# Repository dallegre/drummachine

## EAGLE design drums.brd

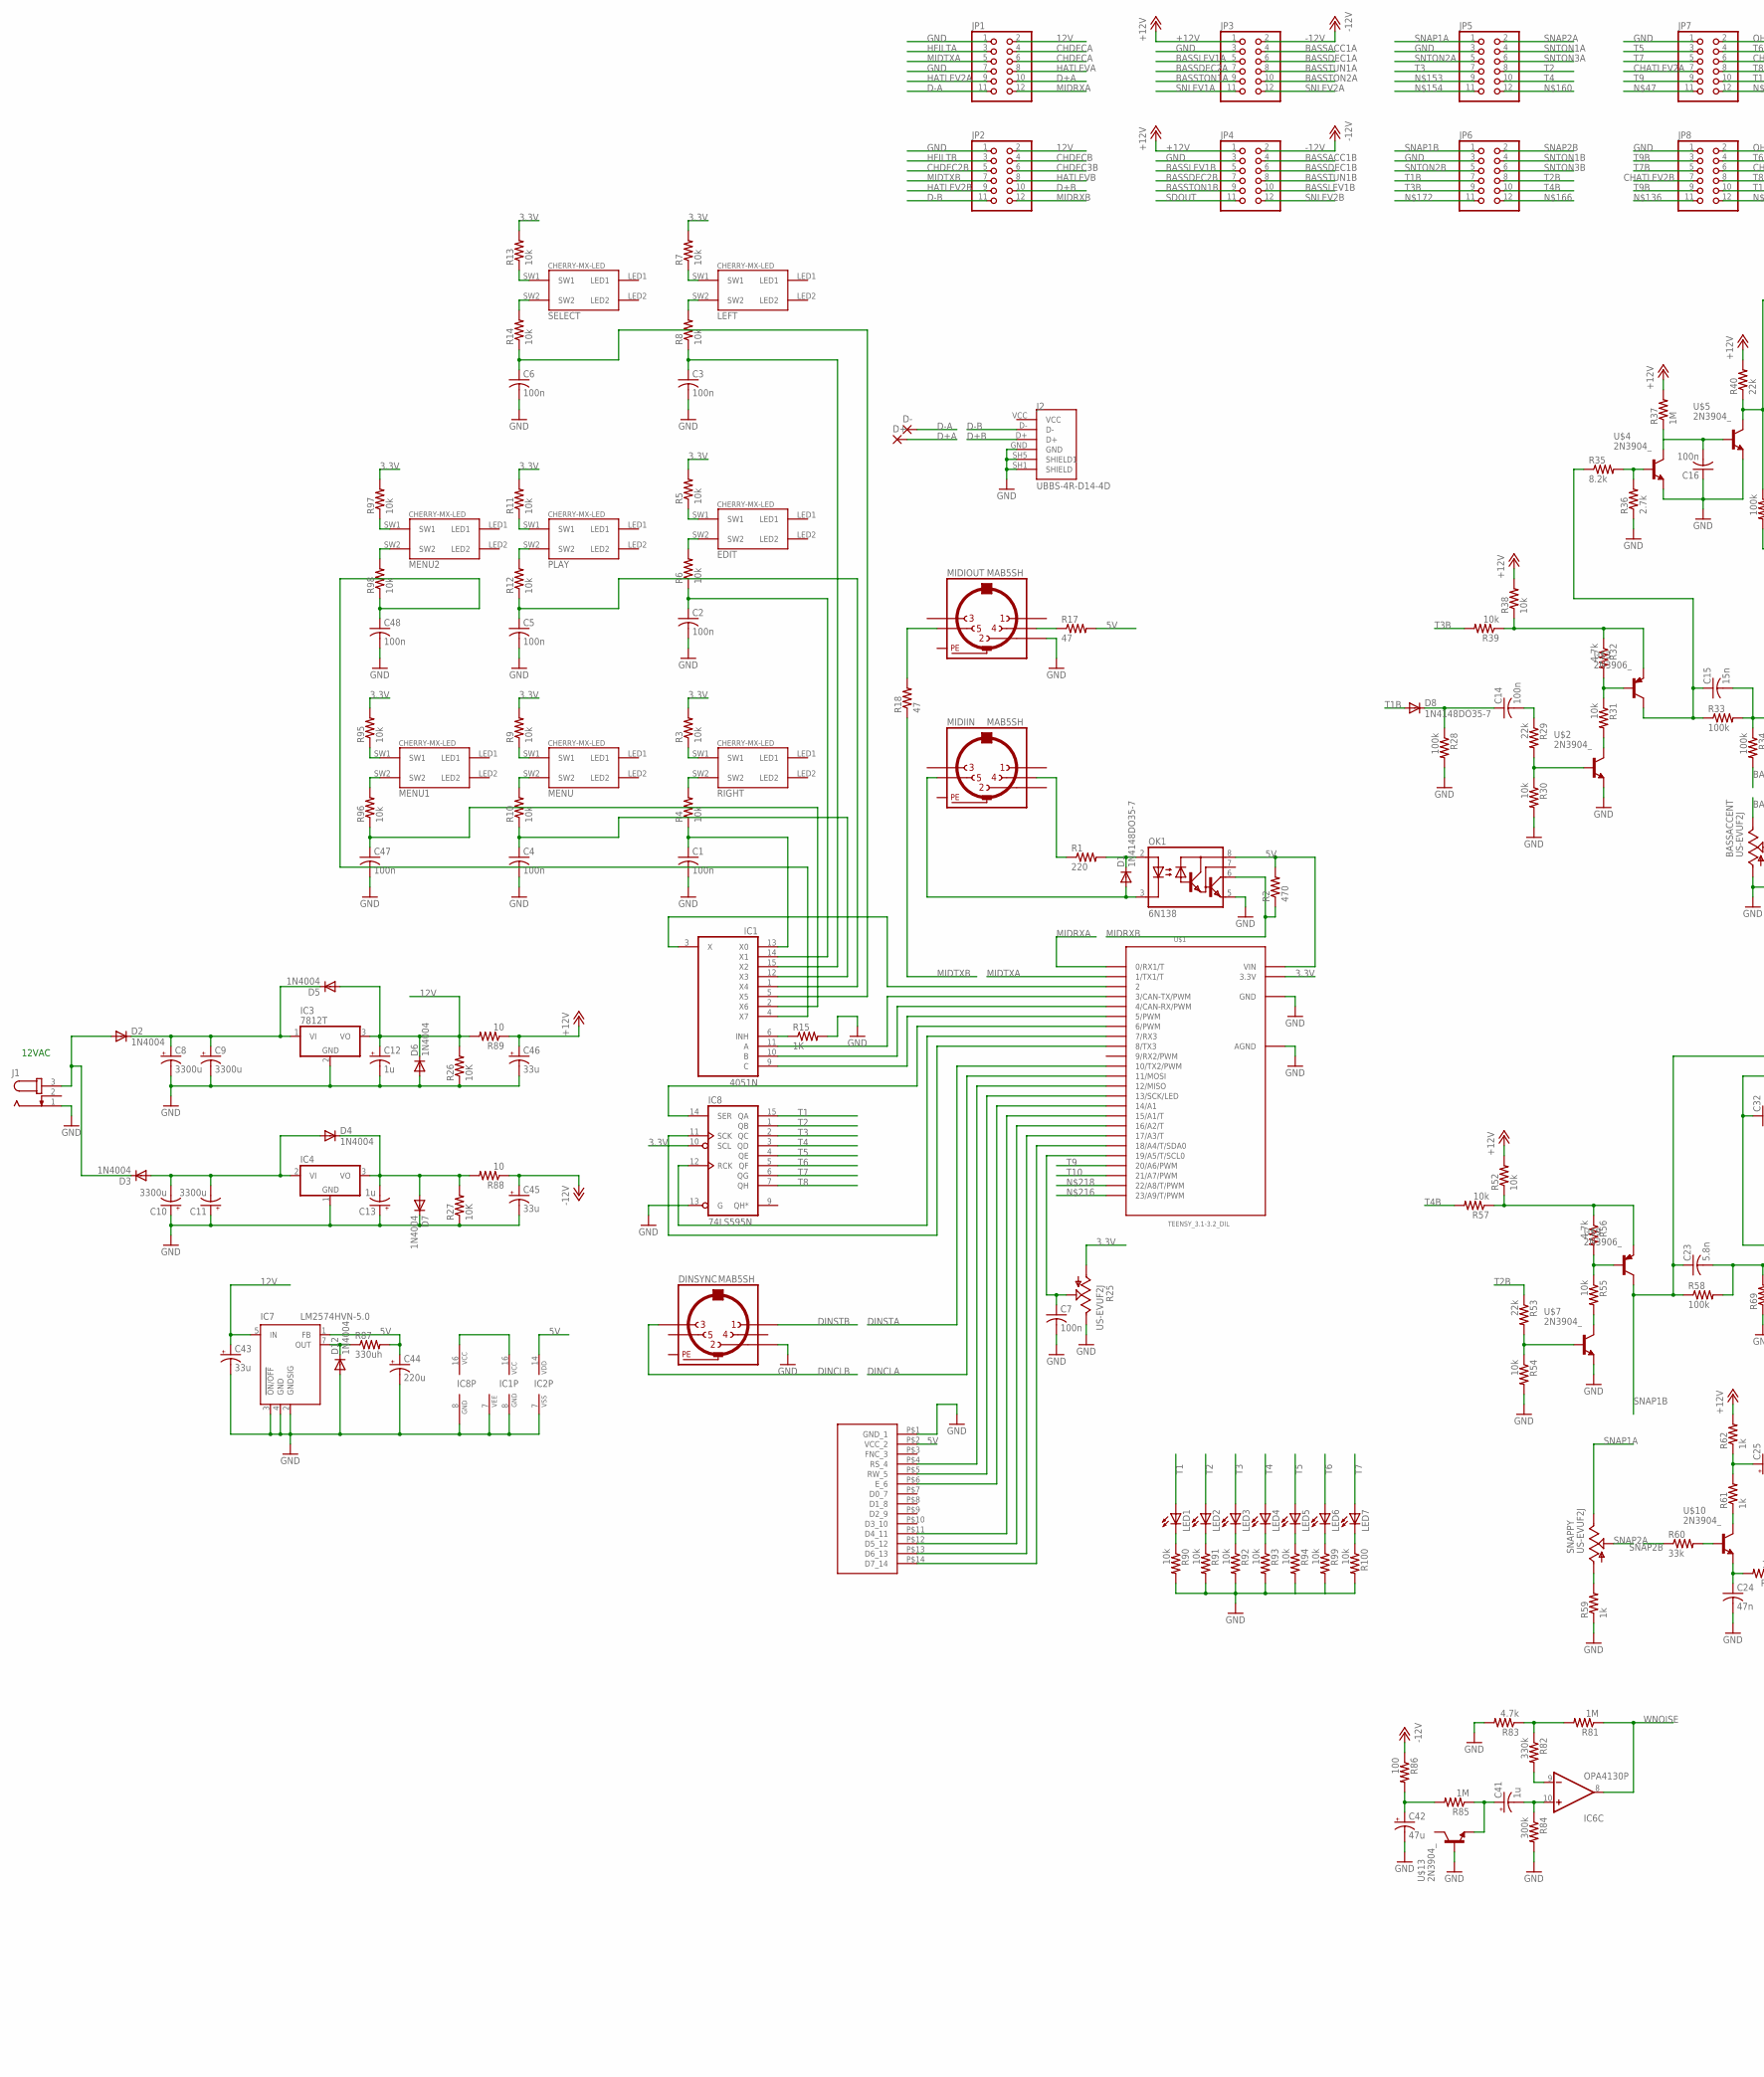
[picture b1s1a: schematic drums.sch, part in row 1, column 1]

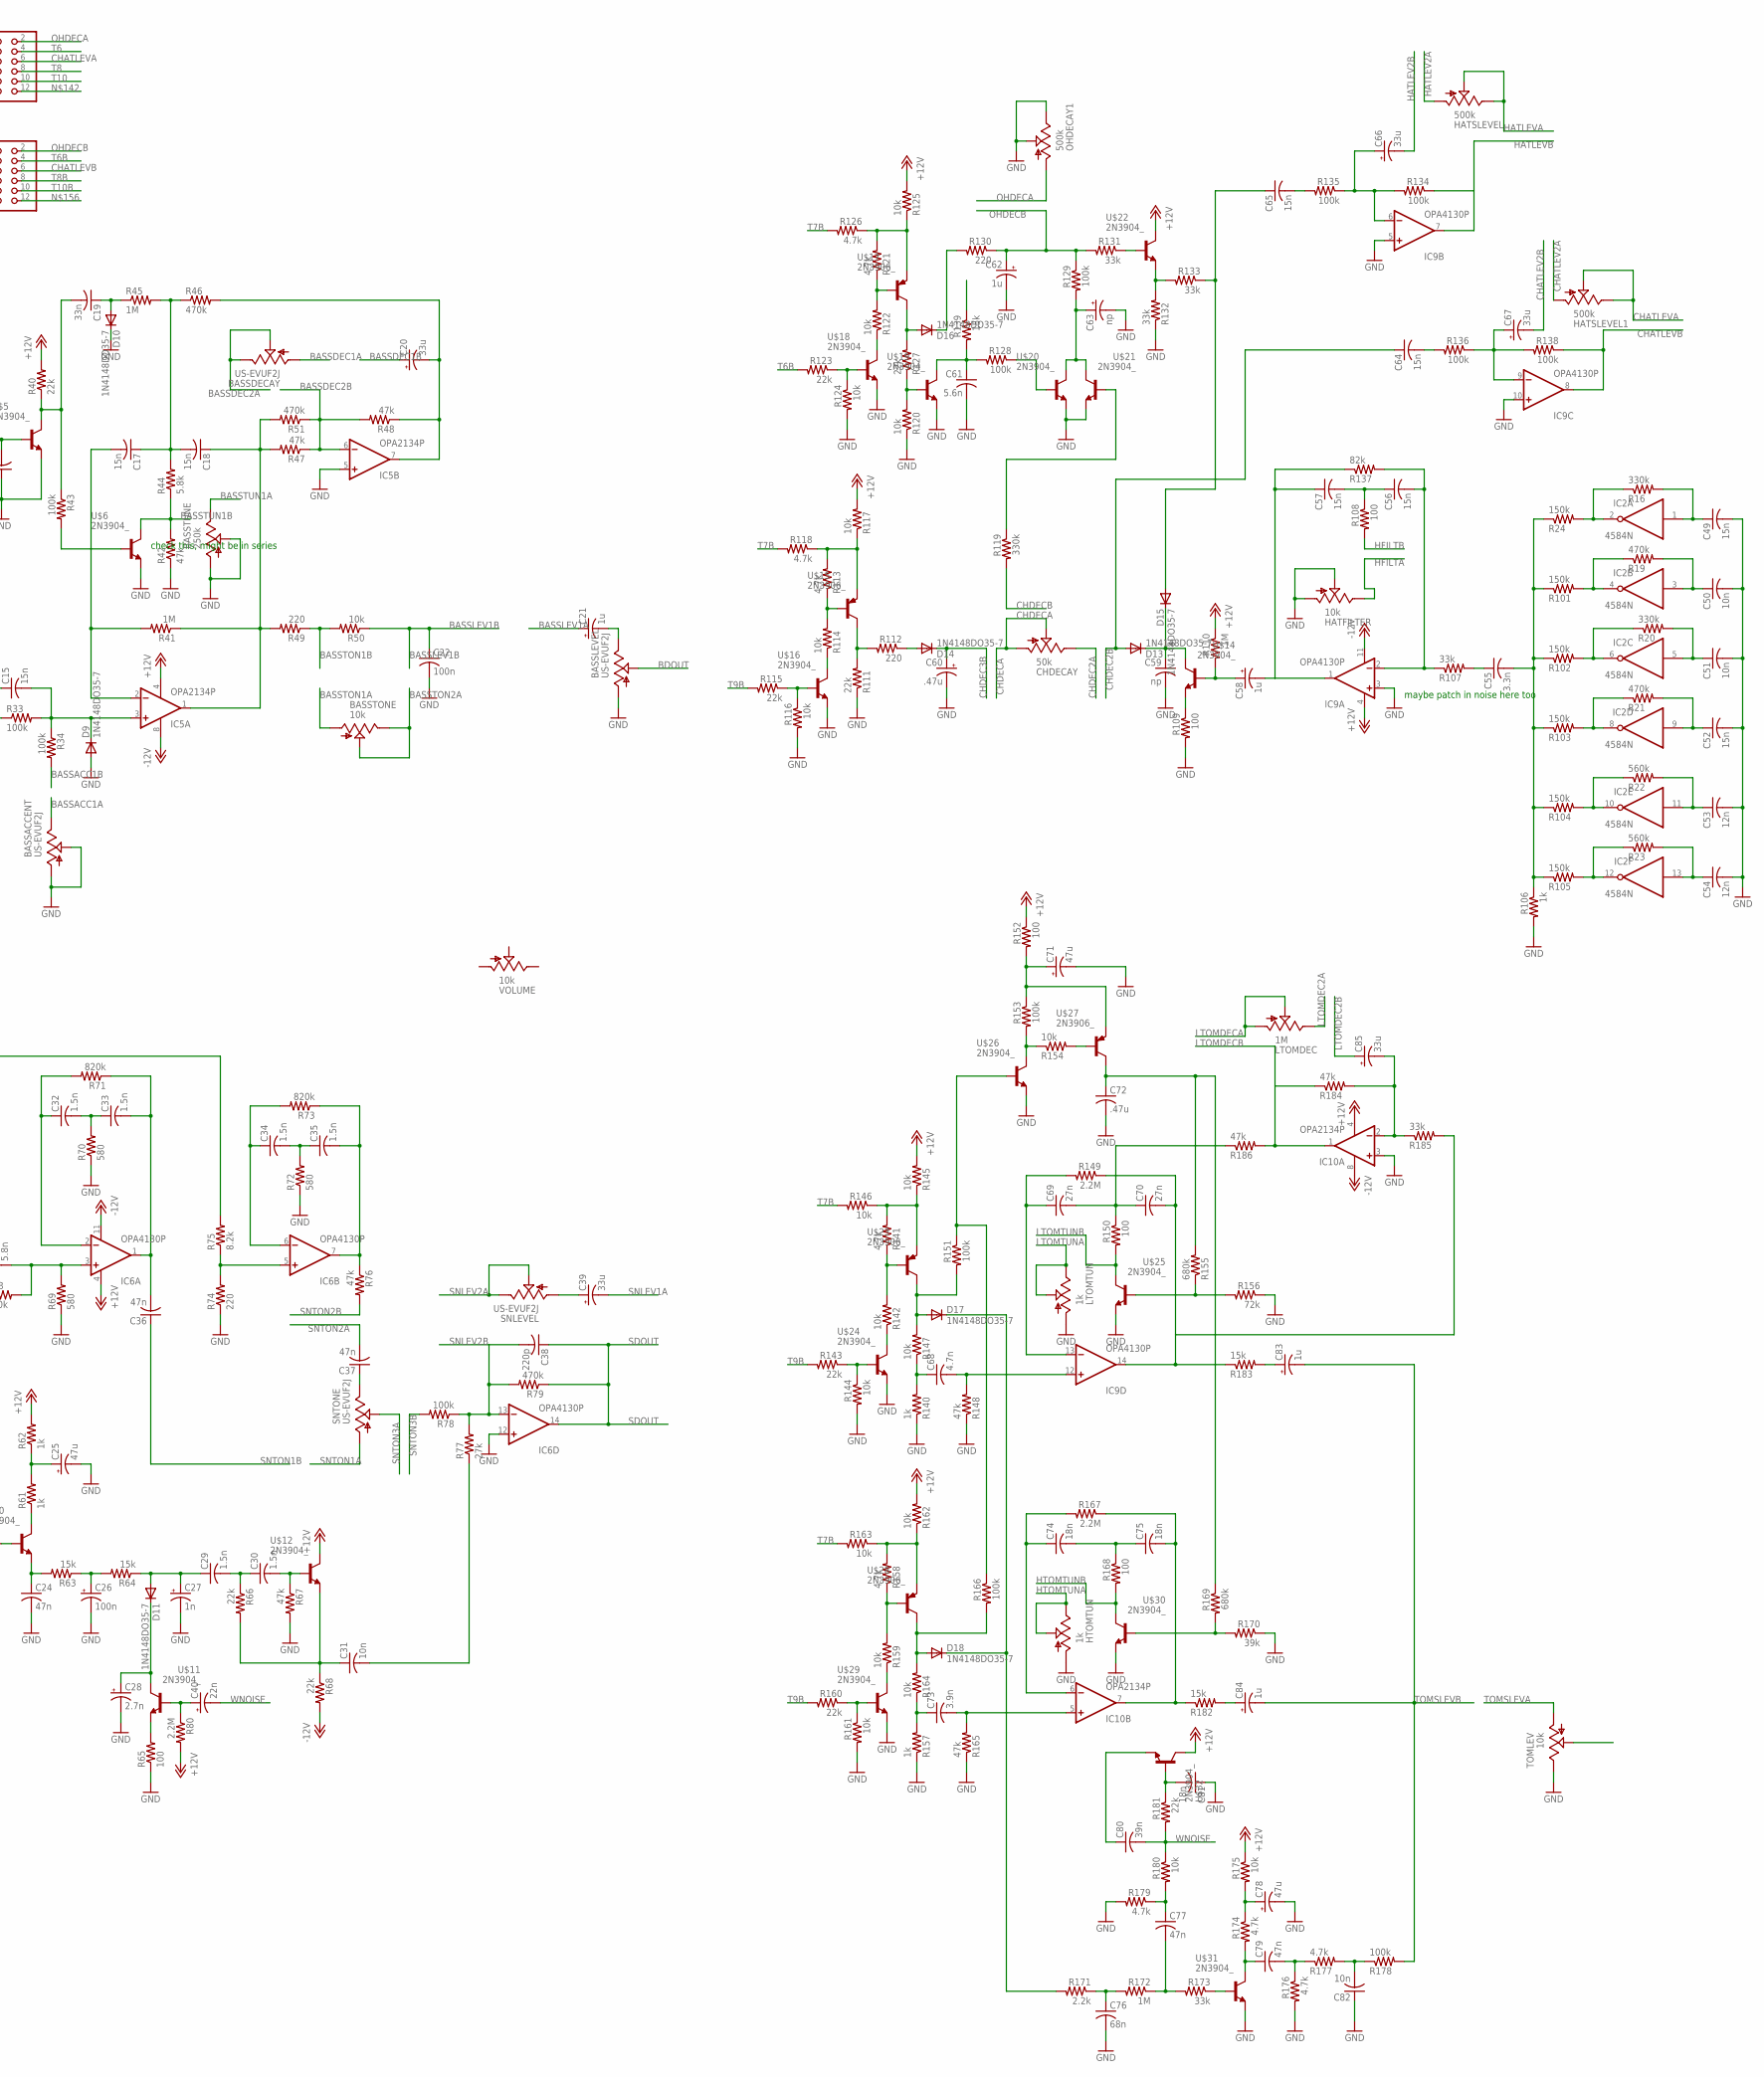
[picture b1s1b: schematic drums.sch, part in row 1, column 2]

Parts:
BASSACCENT: US-EVUF2J; EVUFXJ
BASSDECAY: US-EVUF2J; EVUFXJ
BASSLEVEL: US-EVUF2J; EVUFXJ
BASSTONE: 10k; EVUFXJ
BASSTUNE: 250k; EVUFXJ
C1, C2, C3, C4, C5, C6, C7, C14, C16, C22, C47, C48: 100n; C050-025X075
C8, C9, C10, C11: 3300u; E5-10,5
C12, C13, C21, C41, C58, C62, C83, C84: 1u; E2-5
C15, C17, C18, C49, C52, C56, C57, C64, C65: 15n; C050-025X075
C19: 33n; C050-025X075
C20, C39, C43, C45, C46, C66, C67, C85: 33u; E2-5
C23: 5.8n; C050-025X075
C24, C36, C37, C77, C79: 47n; C050-025X075
C25, C42, C71, C78: 47u; E2-5
C26: 100n; E2-5
C27: 1n; E2-5
C28: 2.7n; E2-5
C29, C30, C32, C33, C34, C35: 1.5n; C050-025X075
C31, C50, C51, C82: 10n; C050-025X075
C38: 220p; C050-025X075
C40: 22n; E2-5
C44: 220u; E2-5
C53, C54: 12n; C050-025X075
C55: 3.3n; C050-025X075
C59: np; C050-025X075
C60: .47u; E2-5
C61: 5.6n; C050-025X075
C63: np; E2-5
C68: 4.7n; C050-025X075
C69, C70: 27n; C050-025X075
C72: .47u; C050-025X075
C73: 3.9n; C050-025X075
C74, C75, C81: 18n; C050-025X075
C76: 68n; C050-025X075
C80: 39n; C050-025X075
CHDECAY: 50k; EVUFXJ
D1, D8, D9, D10, D11, D13, D14, D15, D16, D17, D18: 1N4148DO35-7; DO35-7
D2, D3, D4, D5, D6, D7, D12: 1N4004; DO41-10
D+: 2,0/0,9-R
D-: 2,0/0,9-R
DINSYNC: MAB5SH
EDIT: CHERRY-MX-LED
HATFILTER: 10k; EVUFXJ
HATSLEVEL, HATSLEVEL1: 500k; EVUFXJ
HTOMTUN: 1k; EVUFXJ
IC1: 4051N; DIL16
IC2: 4584N; DIL14
IC3: 7812T; TO220H
IC4: 7906T; TO220H
IC5, IC10: OPA2134P; DIL08
IC6, IC9: OPA4130P; DIL14
IC7: LM2574HVN-5.0; DIL08
IC8: 74LS595N; DIL16
J1: JACK-PLUG0; SPC4077
J2: UBBS-4R-D14-4D; JST_UBBS-4R-D14-4D
JP1, JP2, JP3, JP4, JP5, JP6, JP7, JP8: PINHD-2X6; 2X06
LED1, LED2, LED3, LED4, LED5, LED6, LED7: LED5MM
LEFT: CHERRY-MX-LED
LTOMDEC: 1M; EVUFXJ
LTOMTUN: 1k; EVUFXJ
MENU, MENU1, MENU2: CHERRY-MX-LED
MIDIIN: MAB5SH
MIDIOUT: MAB5SH
OHDECAY1: 500k; EVUFXJ
OK1: 6N138; DIL08
PLAY: CHERRY-MX-LED
R1, R49, R74, R112, R130: 220; 0207/2V
R2: 470; 0207/2V
R3, R4, R5, R6, R7, R8, R9, R10, R11, R12, R13, R14, R30, R31, R38, R39, R50, R52, R54, R55, R57, R90, R91, R92, R93, R94, R95, R96, R97, R98, R99, R100, R114, R116, R117, R120, R122, R124, R125, R142, R144, R145, R146, R147, R154, R159, R161, R162, R163, R164, R175, R180: 10k; 0207/2V
R15: 1K; 0207/2V
R16, R20, R82, R119: 330k; 0207/2V
R17, R18: 47; 0207/2V
R19, R21, R46, R51, R79: 470k; 0207/2V
R22, R23: 560k; 0207/2V
R24, R101, R102, R103, R104, R105: 150k; 0207/2V
R25: US-EVUF2J; EVUFXJ
R26, R27: 10K; 0207/7
R28, R33, R34, R43, R58, R78, R128, R129, R134, R135, R136, R138, R151, R153, R166, R178: 100k; 0207/2V
R29, R40, R53, R66, R68, R111, R115, R123, R127, R143, R160, R181: 22k; 0207/2V
R32, R56, R83, R113, R118, R121, R126, R141, R158, R174, R176, R177, R179: 4.7k; 0207/2V
R35, R75: 8.2k; 0207/2V
R36: 2.7k; 0207/2V
R37, R41, R45, R81, R85, R110, R172: 1M; 0207/2V
R42, R47, R48, R67, R76, R148, R165, R184, R186: 47k; 0207/2V
R44: 5.8k; 0207/2V
R59, R61, R62, R106, R140, R157: 1k; 0207/2V
R60, R107, R131, R132, R133, R173, R185: 33k; 0207/2V
R63, R64, R139, R182, R183: 15k; 0207/2V
R65, R86, R108, R109, R150, R152, R168: 100; 0207/2V
R69, R70, R72: 580; 0207/2V
R71, R73: 820k; 0207/2V
R77: 27k; 0207/2V
R80, R149, R167: 2.2M; 0207/2V
R84: 300k; 0207/2V
R87: 330uh; 0207/2V
R88, R89: 10; 0207/7
R137: 82k; 0207/2V
R155, R169: 680k; 0207/2V
R156: 72k; 0207/2V
R170: 39k; 0207/2V
R171: 2.2k; 0207/2V
RIGHT: CHERRY-MX-LED
SELECT: CHERRY-MX-LED
SNAPPY: US-EVUF2J; EVUFXJ
SNLEVEL: US-EVUF2J; EVUFXJ
SNTONE: US-EVUF2J; EVUFXJ
TOMLEV: 10k; EVUFXJ
U$1: TEENSY_3.1-3.2_DIL; TEENSY_3.0-3.2&LC_DIL
U$2, U$4, U$5, U$6, U$7, U$10, U$11, U$12, U$13, U$14, U$16, U$18, U$19, U$20, U$21, U$22, U$24, U$25, U$26, U$29, U$30, U$31, U$32: 2N3904_; TO92-EBC
U$3, U$9, U$15, U$17, U$23, U$27, U$28: 2N3906_; TO92-EBC
U$8: CU20045-UW
VOLUME: 10k; EVUFXJ

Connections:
3.3V: IC1.16 (VCC), IC8.10 (SCL), IC8.16 (VCC), R3.2, R5.2, R7.2, R9.2, R11.2, R13.2, R25.1 (A), R95.2, R97.2, U$1.3.3V
5V: C44.+, IC2.14 (VDD), IC7.1 (FB), OK1.8 (VCC), R2.2, R17.2, R87.2, U$1.VIN, U$8.P$2 (VCC_2)
12V: C12.+, C43.+, D5.A, D6.C, IC3.3 (VO), IC7.5 (IN), JP1.2, JP2.2, R26.2, R89.2
+12V: C46.+, IC5.4 (V-), IC6.4 (V+), IC9.4 (V+), IC10.4 (V-), JP3.1, JP4.1, R37.2, R38.2, R40.2, R52.2, R62.2, R80.2, R89.1, R110.1, R117.2, R125.2, R145.2, R152.1, R162.2, R175.1, U$12.E (C), U$22.E (C), U$32.E (C)
-12V: C45.+, IC5.8 (V+), IC6.11 (V-), IC9.11 (V-), IC10.8 (V+), JP3.2, JP4.2, R68.2, R86.1, R88.1
BASSACC1A: BASSACCENT.3 (E), JP3.4
BASSACC1B: JP4.4, R34.2
BASSDEC1A: BASSDECAY.1 (A), JP3.6
BASSDEC1B: C20.+, JP4.6
BASSDEC2A: BASSDECAY.2 (S), BASSDECAY.3 (E), JP3.7
BASSDEC2B: IC5.6 (-IN), JP4.7, R47.1, R48.2, R51.1
BASSLEV1A: C21.+, JP3.5
BASSLEV1B: C22.1, JP4.5, JP4.10, R50.1
BASSTON1A: BASSTONE.1 (A), JP3.9
BASSTON1B: JP4.9, R49.1, R50.2
BASSTON2A: BASSTONE.2 (S), BASSTONE.3 (E), JP3.10
BASSTUN1A: BASSTUNE.3 (E), JP3.8
BASSTUN1B: JP4.8, R42.2, R44.1, U$6.E (C)
BDOUT: BASSLEVEL.2 (S)
CHATLEV2A: HATSLEVEL1.1 (A), JP7.7
CHATLEV2B: C67.-, JP8.7
CHATLEVA: HATSLEVEL1.2 (S), HATSLEVEL1.3 (E), JP7.6
CHATLEVB: IC9.8 (OUT), JP8.6, R138.1
CHDEC2A: CHDECAY.3 (E)
CHDEC2B: C64.1, D13.A, JP2.5
CHDEC3B: C60.+, D14.C, JP2.6
CHDECA: CHDECAY.1 (A), CHDECAY.2 (S), JP1.4, JP1.6
CHDECB: JP2.4, R119.2
D+A: D+.1, JP1.10
D+B: J2.D+, JP2.10
D-A: D-.1, JP1.11
D-B: J2.D-, JP2.11
DINCLA: U$1.11 (11/MOSI)
DINCLB: DINSYNC.3
DINSTA: U$1.10 (10/TX2/PWM)
DINSTB: DINSYNC.1
GND: BASSACCENT.1 (A), BASSACCENT.2 (S), BASSLEVEL.1 (A), BASSTUNE.1 (A), BASSTUNE.2 (S), C1.2, C2.2, C3.2, C4.2, C5.2, C6.2, C7.2, C8.-, C9.-, C10.+, C11.+, C12.-, C13.+, C16.1, C22.2, C24.2, C25.-, C26.-, C27.-, C28.-, C42.-, C43.-, C44.-, C45.-, C46.-, C47.2, C48.2, C49.2, C50.2, C51.2, C52.2, C53.2, C54.2, C59.2, C60.-, C61.2, C62.-, C63.-, C71.-, C72.2, C76.2, C78.-, C81.1, C82.1, D6.A, D7.C, D9.A, D10.C, D12.A, DINSYNC.2, HATFILTER.1 (A), HATFILTER.2 (S), HTOMTUN.1 (A), IC1.7 (VEE), IC1.8 (GND), IC2.7 (VSS), IC3.2 (GND), IC4.1 (GND), IC5.5 (+IN), IC6.12 (+IN), IC7.2 (GNDSIG), IC7.3 (!ON/OFF), IC7.4 (GND), IC8.8 (GND), IC8.13 (G), IC9.3 (+IN), IC9.5 (+IN), IC9.10 (+IN), IC10.3 (+IN), J1.1, J2.GND, J2.SH1 (SHIELD), J2.SH5 (SHIELD1), JP1.1, JP1.7, JP2.1, JP3.3, JP4.3, JP5.3, JP6.3, JP7.1, JP8.1, LTOMTUN.1 (A), MIDIOUT.2, OHDECAY1.2 (S), OHDECAY1.3 (E), OK1.5 (GND), R15.2, R25.3 (E), R26.1, R27.1, R28.2, R30.2, R36.1, R42.1, R54.2, R59.1, R65.1, R67.2, R69.1, R70.1, R72.1, R74.1, R83.2, R84.2, R90.2, R91.2, R92.2, R93.2, R94.2, R106.2, R109.2, R111.1, R116.2, R120.1, R124.2, R132.1, R140.1, R144.2, R148.1, R156.1, R157.1, R161.2, R165.1, R170.1, R176.2, R179.2, TOMLEV.3 (E), U$1.AGND, U$1.GND, U$2.C (E), U$4.C (E), U$5.C (E), U$6.C (E), U$7.C (E), U$8.P$1 (GND_1), U$13.B, U$16.C (E), U$18.C (E), U$19.C (E), U$20.C (E), U$21.C (E), U$24.C (E), U$25.C (E), U$26.C (E), U$29.C (E), U$30.C (E), U$31.C (E)
GND1: R99.2
GND2: R100.2
HATLEV2A: HATSLEVEL.1 (A), JP1.9
HATLEV2B: C66.-, JP2.9
HATLEVA: HATSLEVEL.2 (S), HATSLEVEL.3 (E), JP1.8
HATLEVB: IC9.7 (OUT), JP2.8, R134.1
HFILTA: HATFILTER.3 (E), JP1.3
HFILTB: JP2.3, R108.2
HTOMTUNA: HTOMTUN.2 (S), HTOMTUN.3 (E)
HTOMTUNB: R168.2, U$30.E (C)
LTOMDEC2A: LTOMDEC.3 (E)
LTOMDEC2B: C85.+
LTOMDECA: LTOMDEC.1 (A), LTOMDEC.2 (S)
LTOMDECB: IC10.1 (OUT), R184.1, R186.2
LTOMTUNA: LTOMTUN.2 (S), LTOMTUN.3 (E)
LTOMTUNB: R150.2, U$25.E (C)
MIDRXA: JP1.12, U$1.0 (0/RX1/T)
MIDRXB: JP2.12, OK1.6 (VO), R2.1
MIDTXA: JP1.5, U$1.1 (1/TX1/T)
MIDTXB: JP2.7, R18.1
unnamed: R4.2, RIGHT.SW2
unnamed: C67.+, IC9.9 (-IN), R136.1, R138.2
unnamed: C1.1, IC1.13 (X0), R4.1
unnamed: D1.C, OK1.2 (A), R1.2
unnamed: D1.A, MIDIIN.5, OK1.3 (C)
unnamed: EDIT.SW1, R5.1
unnamed: IC1.3 (X), U$1.2
unnamed: IC1.11 (A), U$1.3 (3/CAN-TX/PWM)
unnamed: IC1.10 (B), U$1.4 (4/CAN-RX/PWM)
unnamed: IC1.9 (C), U$1.5 (5/PWM)
unnamed: R3.1, RIGHT.SW1
unnamed: EDIT.SW2, R6.2
unnamed: C2.1, IC1.14 (X1), R6.1
unnamed: LEFT.SW1, R7.1
unnamed: LEFT.SW2, R8.2
unnamed: C3.1, IC1.15 (X2), R8.1
unnamed: MENU.SW1, R9.1
unnamed: MENU.SW2, R10.2
unnamed: C4.1, IC1.12 (X3), R10.1
unnamed: PLAY.SW1, R11.1
unnamed: PLAY.SW2, R12.2
unnamed: C5.1, IC1.1 (X4), R12.1
unnamed: R13.1, SELECT.SW1
unnamed: R14.2, SELECT.SW2
unnamed: C6.1, IC1.5 (X5), R14.1
unnamed: MIDIIN.4, R1.1
unnamed: IC1.6 (INH), R15.1
unnamed: IC8.12 (RCK), U$1.7 (7/RX3)
unnamed: IC8.14 (SER), U$1.6 (6/PWM)
unnamed: IC8.11 (SCK), U$1.8 (8/TX3)
unnamed: C52.1, IC2.9 (I), R21.2
unnamed: MIDIOUT.4, R17.1
unnamed: MIDIOUT.5, R18.2
unnamed: D17.A, R147.2, R151.2, U$23.E (C)
unnamed: R141.1, R142.2, U$23.B
unnamed: R141.2, R145.1, R146.1, U$23.C (E)
unnamed: R142.1, U$24.E (C)
unnamed: U$1.12 (12/MISO), U$8.P$4 (RS_4)
unnamed: U$1.13 (13/SCK/LED), U$8.P$5 (RW_5)
unnamed: U$1.14/A0 (14/A1), U$8.P$6 (E_6)
unnamed: U$1.15/A1 (15/A1/T), U$8.P$11 (D4_11)
unnamed: U$1.16/A2 (16/A2/T), U$8.P$12 (D5_12)
unnamed: U$1.17/A3 (17/A3/T), U$8.P$13 (D6_13)
unnamed: U$1.18/A4 (18/A4/T/SDA0), U$8.P$14 (D7_14)
unnamed: R143.1, R144.1, U$24.B
unnamed: IC2.8 (O), R21.1, R103.2
unnamed: C68.1, R140.2, R147.1
unnamed: C7.1, R25.2 (S), U$1.19/A5 (19/A5/T/SCL0)
unnamed: C8.+, C9.+, D2.C, D5.C, IC3.1 (VI)
unnamed: C10.-, C11.-, D3.A, D4.A, IC4.2 (VI)
unnamed: D2.A, D3.C, J1.3
unnamed: C14.1, D8.C, R28.1
unnamed: C14.2, R29.1
unnamed: R29.2, R30.1, U$2.B
unnamed: R31.2, U$2.E (C)
unnamed: R31.1, R32.2, U$3.B
unnamed: R32.1, R38.1, R39.1, U$3.C (E)
unnamed: C15.1, R33.1, R35.1, U$3.E (C)
unnamed: C17.2, IC5.2 (-IN), R41.2
unnamed: C15.2, D9.C, IC5.3 (+IN), R33.2, R34.1
unnamed: C19.2, R40.1, R43.1, U$5.E (C)
unnamed: C18.1, IC5.1 (OUT), R41.1, R47.2, R49.2, R51.2
unnamed: R35.2, R36.2, U$4.B
unnamed: IC2.2 (O), R16.1, R24.2
unnamed: C16.2, R37.1, U$4.E (C), U$5.B
unnamed: C23.2, IC6.3 (+IN), R58.2, R69.2
unnamed: R43.2, U$6.B
unnamed: C49.1, IC2.1 (I), R16.2
unnamed: C17.1, C18.2, R44.2, R45.2, R46.1
unnamed: C19.1, D10.A, R45.1
unnamed: C50.1, IC2.3 (I), R19.2
unnamed: IC2.4 (O), R19.1, R101.2
unnamed: BASSLEVEL.3 (E), C21.-
unnamed: C20.-, IC5.7 (OUT), R46.2, R48.1
unnamed: R59.2, SNAPPY.1 (A)
unnamed: IC2.6 (O), R20.1, R102.2
unnamed: C51.1, IC2.5 (I), R20.2
unnamed: R53.2, R54.1, U$7.B
unnamed: R55.2, U$7.E (C)
unnamed: R55.1, R56.2, U$9.B
unnamed: R52.1, R56.1, R57.1, U$9.C (E)
unnamed: C53.1, IC2.11 (I), R22.2
unnamed: IC2.10 (O), R22.1, R104.2
unnamed: R60.2, U$10.B
unnamed: R61.1, U$10.E (C)
unnamed: C25.+, R61.2, R62.1
unnamed: C24.1, R63.2, U$10.C (E)
unnamed: C26.+, R63.1, R64.2
unnamed: C27.+, C29.1, D11.A, R64.1
unnamed: R65.2, U$11.C (E)
unnamed: C29.2, C30.1, R66.1
unnamed: C28.+, D11.C, U$11.E (C)
unnamed: C30.2, R67.1, U$12.B
unnamed: C31.1, R66.2, R68.1, U$12.C (E)
unnamed: C32.2, C33.1, R70.2
unnamed: C33.2, C36.2, IC6.1 (OUT), R71.1
unnamed: C32.1, IC6.2 (-IN), R71.2
unnamed: C34.2, C35.1, R72.2
unnamed: C35.2, IC6.7 (OUT), R73.1, R76.1
unnamed: C34.1, IC6.6 (-IN), R73.2
unnamed: IC6.5 (+IN), R74.2, R75.1
unnamed: C37.1, SNTONE.3 (E)
unnamed: IC2.12 (O), R23.1, R105.2
unnamed: C54.1, IC2.13 (I), R23.2
unnamed: C31.2, R77.1
unnamed: C58.+, R110.2, U$14.B
unnamed: C55.2, R24.1, R101.1, R102.1, R103.1, R104.1, R105.1, R106.1
unnamed: LED1.K (C), R90.1
unnamed: C40.+, R80.1, U$11.B
unnamed: IC6.9 (-IN), R82.2
unnamed: C39.+, SNLEVEL.1 (A)
unnamed: LED2.K (C), R91.1
unnamed: R81.2, R82.1, R83.1
unnamed: C41.-, IC6.10 (+IN), R84.1
unnamed: C41.+, R85.1, U$13.C (E)
unnamed: C42.+, R85.2, R86.2
unnamed: D12.C, IC7.7 (OUT), R87.1
unnamed: C13.-, D4.C, D7.A, IC4.3 (VO), R27.2, R88.2
unnamed: LED3.K (C), R92.1
unnamed: LED4.K (C), R93.1
unnamed: LED5.K (C), R94.1
unnamed: MENU1.SW1, R95.1
unnamed: MENU1.SW2, R96.2
unnamed: C47.1, IC1.2 (X6), R96.1
unnamed: MENU2.SW1, R97.1
unnamed: MENU2.SW2, R98.2
unnamed: C48.1, IC1.4 (X7), R98.1
unnamed: LED7.K (C), R100.1
unnamed: C68.2, IC9.12 (+IN), R148.2
unnamed: LED6.K (C), R99.1
unnamed: C69.1, IC9.13 (-IN), R149.2
unnamed: C70.2, IC9.14 (OUT), R149.1, R183.1, R185.2
unnamed: C69.2, C70.1, R150.1, R186.1
unnamed: C55.1, R107.2
unnamed: C71.+, R152.2, R153.1, U$27.C (E)
unnamed: C76.1, R171.1, R172.2
unnamed: R153.2, R154.1, U$26.E (C)
unnamed: C56.2, IC9.2 (-IN), R107.1, R137.2
unnamed: C56.1, C57.2, R108.1
unnamed: C57.1, C58.-, IC9.1 (OUT), R137.1
unnamed: R109.1, U$14.C (E)
unnamed: C59.1, D13.C, D15.C, U$14.E (C)
unnamed: C72.1, R155.2, R169.1, U$27.E (C)
unnamed: D14.A, R112.1
unnamed: R113.1, R114.2, U$15.B
unnamed: R111.2, R112.2, U$15.E (C)
unnamed: R113.2, R117.1, R118.1, U$15.C (E)
unnamed: R114.1, U$16.E (C)
unnamed: R115.1, R116.1, U$16.B
unnamed: R154.2, U$27.B
unnamed: R155.1, R156.2, U$25.B
unnamed: D16.A, R127.2, U$17.E (C)
unnamed: R121.1, R122.2, U$17.B
unnamed: R121.2, R125.1, R126.1, U$17.C (E)
unnamed: R122.1, U$18.E (C)
unnamed: R123.1, R124.1, U$18.B
unnamed: C77.2, R172.1, R173.2
unnamed: D18.A, R164.2, R166.2, U$28.E (C)
unnamed: R120.2, R127.1, U$19.B
unnamed: C61.1, R128.2, R139.2, U$19.E (C)
unnamed: C65.1, D15.A, R133.1
unnamed: R128.1, U$20.B
unnamed: C63.+, R129.2, U$20.E (C), U$21.E (C)
unnamed: D16.C, R130.2
unnamed: R158.1, R159.2, U$28.B
unnamed: R131.1, U$22.B
unnamed: R132.2, R133.2, U$22.C (E)
unnamed: R119.1, U$21.B
unnamed: R158.2, R162.1, R163.1, U$28.C (E)
unnamed: C64.2, R136.2
unnamed: C65.2, R135.2
unnamed: C66.+, IC9.6 (-IN), R134.2, R135.1
unnamed: R159.1, U$29.E (C)
unnamed: R160.1, R161.1, U$29.B
unnamed: C73.1, R157.2, R164.1
unnamed: C73.2, IC10.5 (+IN), R165.2
unnamed: R151.1, R166.1, U$26.B
unnamed: D17.C, D18.C, R171.2
unnamed: R173.1, U$31.B
unnamed: C74.1, IC10.6 (-IN), R167.2
unnamed: C75.2, IC10.7 (OUT), R167.1, R182.1
unnamed: C74.2, C75.1, R168.1
unnamed: R169.2, R170.2, U$30.B
unnamed: C79.1, R174.2, U$31.E (C)
unnamed: C78.+, R174.1, R175.2
unnamed: C77.1, R179.1, R180.2
unnamed: C81.2, R181.1, U$32.B
unnamed: C79.2, R176.1, R177.1
unnamed: C80.1, U$32.C (E)
unnamed: C82.2, R177.2, R178.1
unnamed: C85.-, IC10.2 (-IN), R184.2, R185.1
unnamed: C84.+, R182.2
unnamed: C83.+, R183.2
OHDECA: JP7.2, OHDECAY1.1 (A)
OHDECB: C62.+, JP8.2, R129.1, R130.1, R131.2
PE: DINSYNC.PE, DINSYNC.PE@ (PE), MIDIIN.PE, MIDIIN.PE@ (PE), MIDIOUT.PE, MIDIOUT.PE@ (PE)
SDOUT: C38.1, IC6.14 (OUT), JP4.11, R79.1
SNAP1A: JP5.1, SNAPPY.3 (E)
SNAP1B: C23.1, JP6.1, R58.1, R75.2, U$9.E (C)
SNAP2A: JP5.2, SNAPPY.2 (S)
SNAP2B: JP6.2, R60.1
SNLEV1A: C39.-, JP3.11
SNLEV2A: JP3.12, SNLEVEL.2 (S), SNLEVEL.3 (E)
SNLEV2B: C38.2, IC6.13 (-IN), JP4.12, R77.2, R78.1, R79.2
SNTON1A: JP5.4, SNTONE.1 (A)
SNTON1B: C36.1, JP6.4
SNTON2A: C37.2, JP5.5
SNTON2B: JP6.5, R76.2
SNTON3A: JP5.6, SNTONE.2 (S)
SNTON3B: JP6.6, R78.2
T1: IC8.15 (QA), LED1.A
T1B: D8.A, JP6.7
T2: IC8.1 (QB), JP5.8, LED2.A
T2B: JP6.8, R53.1
T3: IC8.2 (QC), JP5.7, LED3.A
T3B: JP6.9, R39.2
T4: IC8.3 (QD), JP5.10, LED4.A
T4B: JP6.10, R57.2
T5: IC8.4 (QE), JP7.3, LED5.A
T6: IC8.5 (QF), JP7.4, LED6.A
T6B: JP8.4, R123.2
T7: IC8.6 (QG), JP7.5, LED7.A
T7B: JP8.5, R118.2, R126.2, R146.2, R163.2
T8: IC8.7 (QH), JP7.8
T8B: JP8.8
T9: JP7.9, U$1.20/A6 (20/A6/PWM)
T9B: JP8.3, JP8.9, R115.2, R143.2, R160.2
T10: JP7.10, U$1.21/A7 (21/A7/PWM)
T10B: JP8.10
TOMSLEVA: TOMLEV.1 (A)
TOMSLEVB: C83.-, C84.-, R178.2
WNOISE: C40.-, C80.2, IC6.8 (OUT), R81.1, R180.1, R181.2

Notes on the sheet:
12VAC
maybe patch in noise here too
check this, might be in series

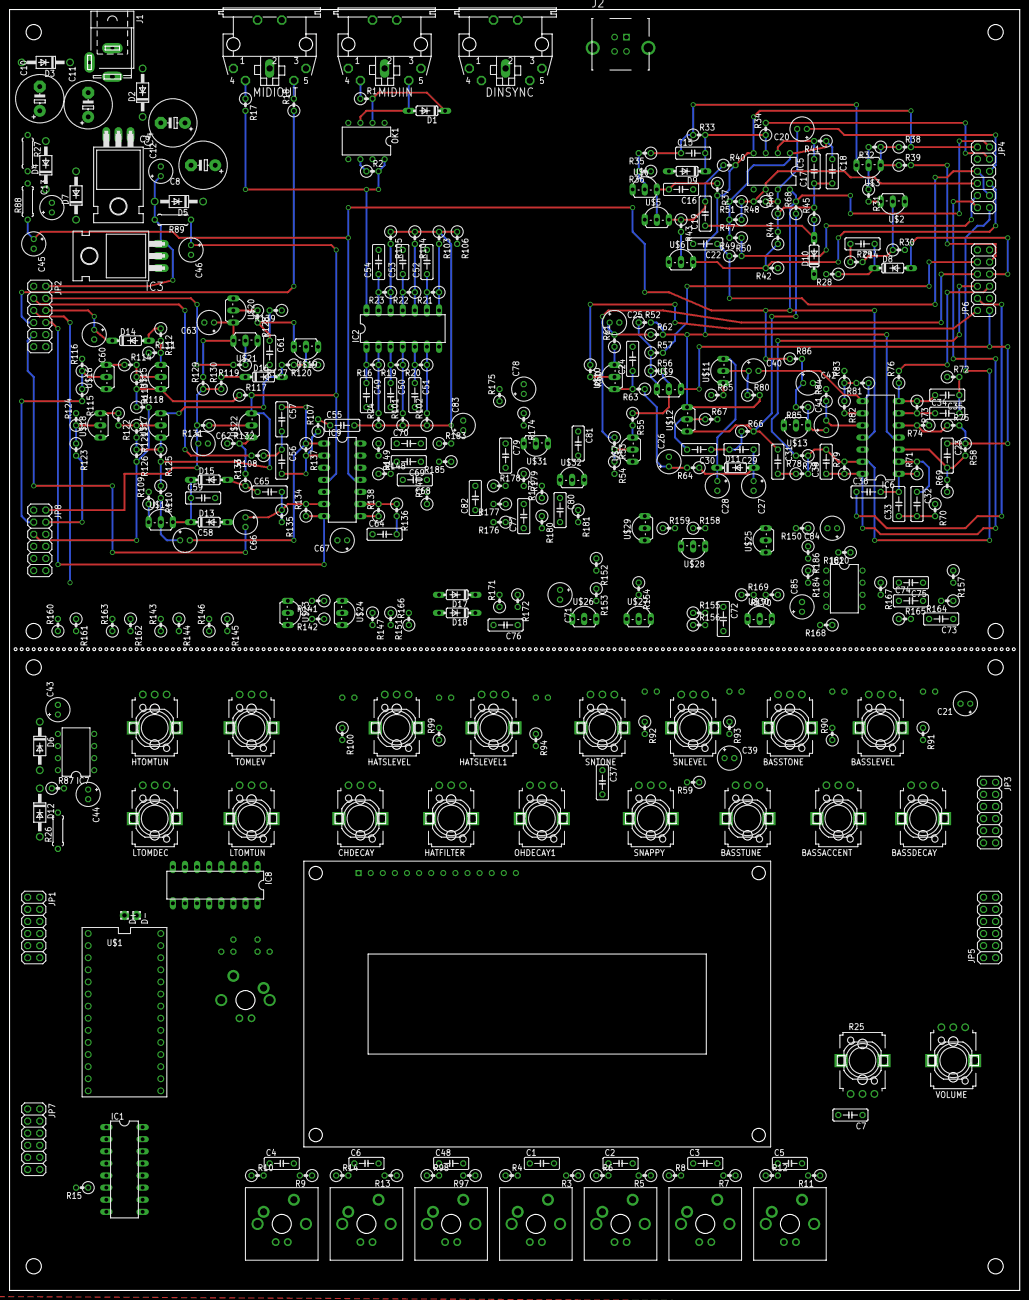
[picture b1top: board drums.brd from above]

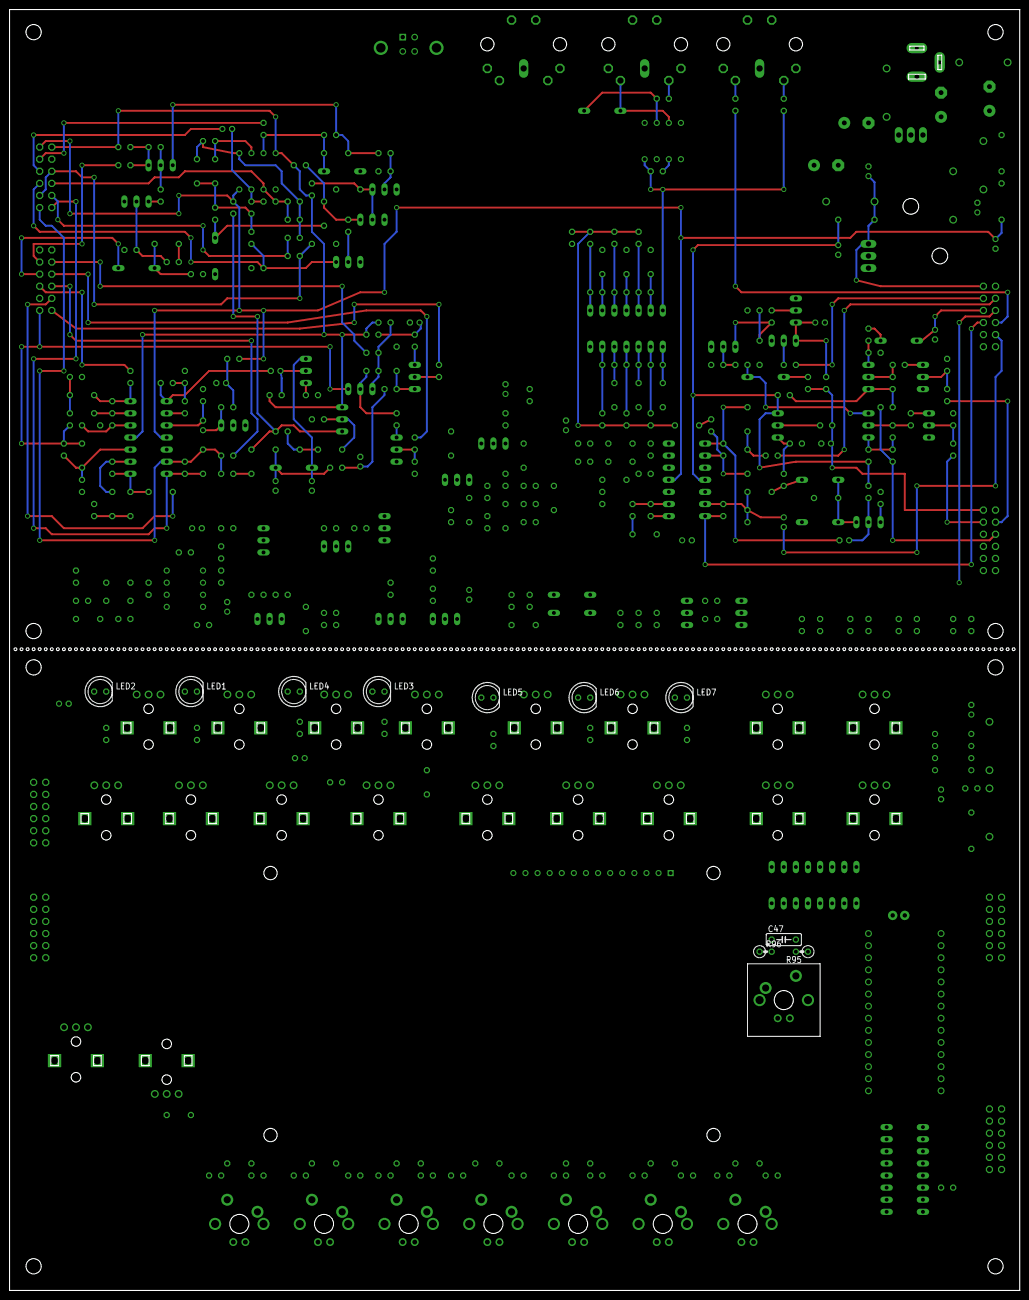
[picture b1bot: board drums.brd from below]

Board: 2 copper layers, 212.1 x 268.9 mm, 380 parts (11 on the bottom side), 276 nets.

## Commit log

2020-06-08 added hihats, buncha stuff
2020-06-09 made hihat layout
2020-06-11 added toms
